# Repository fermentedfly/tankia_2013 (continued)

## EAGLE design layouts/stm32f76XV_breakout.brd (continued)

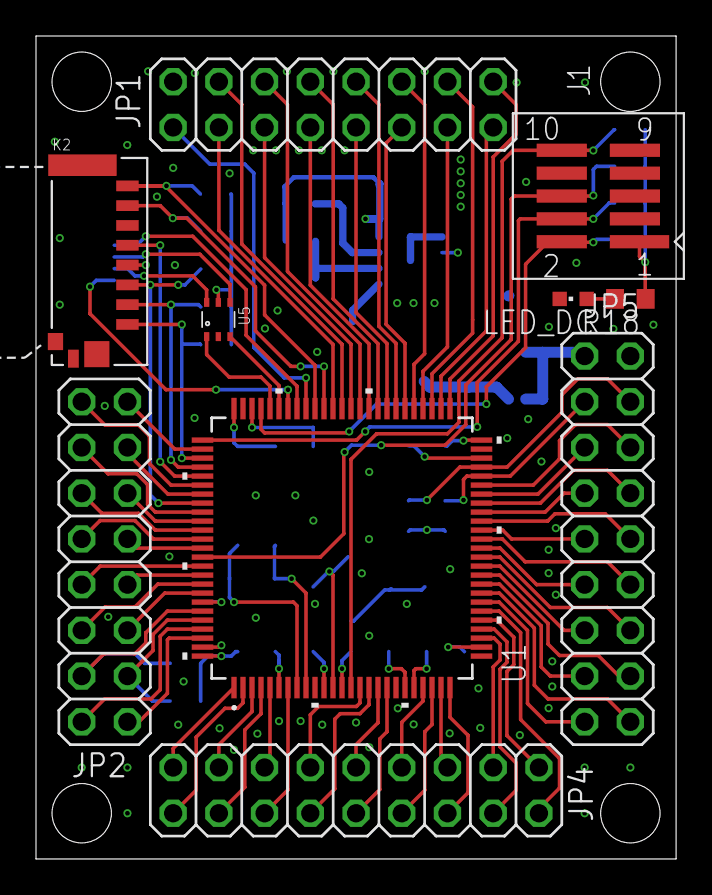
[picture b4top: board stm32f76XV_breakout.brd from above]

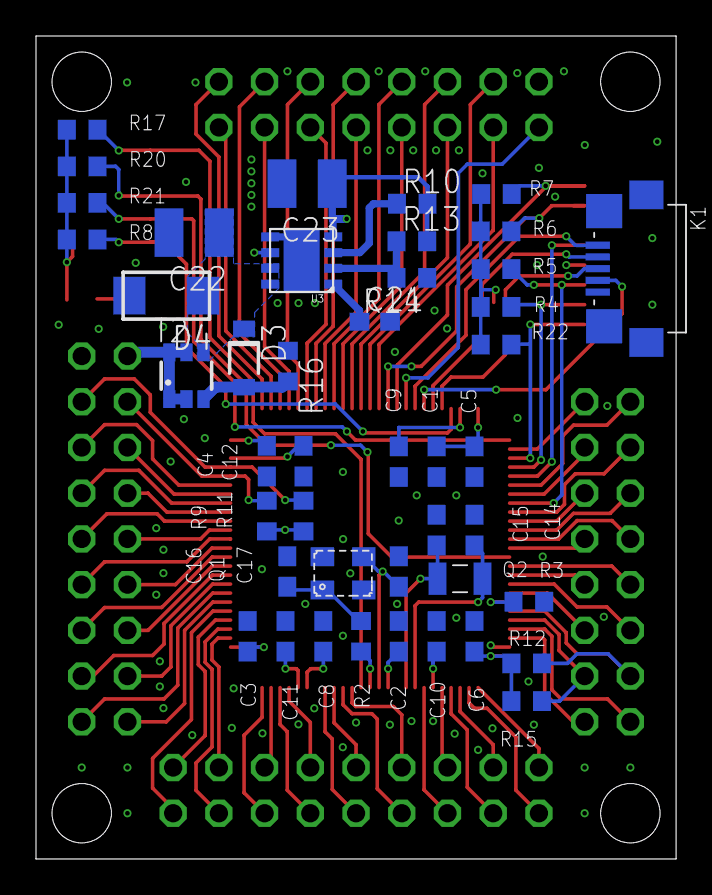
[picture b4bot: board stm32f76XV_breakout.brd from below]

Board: 4 copper layers, 35.6 x 45.7 mm, 54 parts (44 on the bottom side), 98 nets.

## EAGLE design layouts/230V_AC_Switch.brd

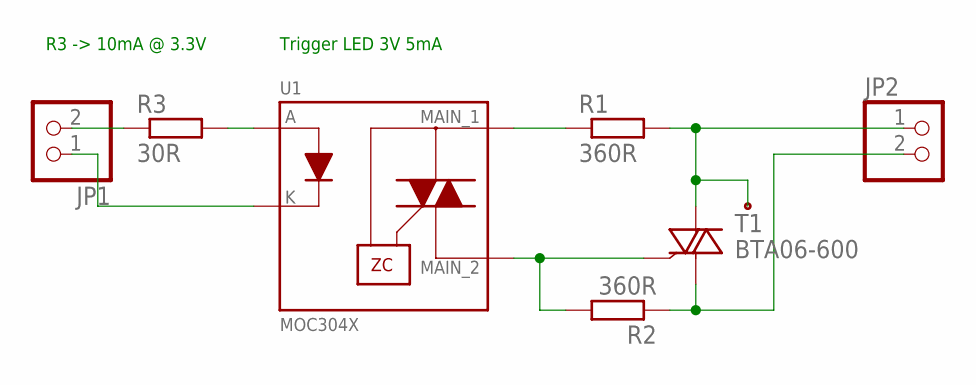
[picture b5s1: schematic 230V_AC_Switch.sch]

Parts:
JP1, JP2: PINHD-1X2; 1X02
R1, R2: 360R; R1206
R3: 30R; R0603
T1: BTA06-600; TO220AB
U1: MOC304X; PDIP

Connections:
EN_+: JP1.2, R3.1
EN_-: JP1.1, U1.2 (K)
unnamed: R2.2, T1.3 (G), U1.4 (MAIN_2)
unnamed: R1.1, U1.6 (MAIN_1)
unnamed: R3.2, U1.1 (A)
OUT: JP2.2, R2.1, T1.1 (A1)
VAC: JP2.1, R1.2, T1.2 (A2), T1.PAD

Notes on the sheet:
Trigger LED 3V 5mA
R3 -> 10mA @ 3.3V

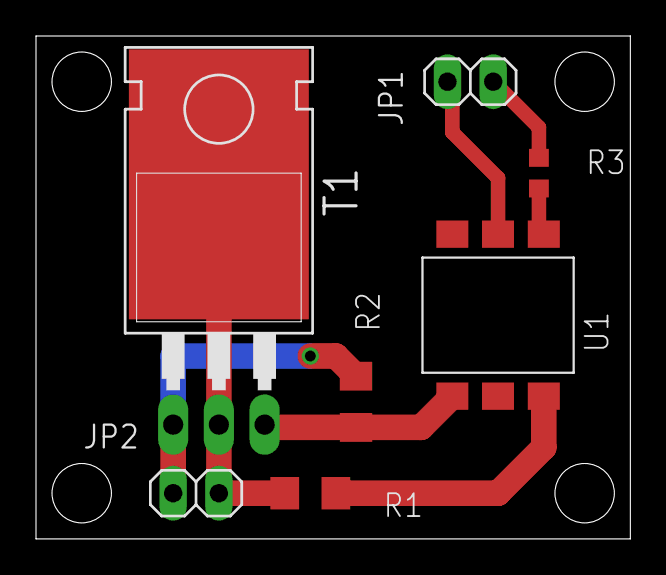
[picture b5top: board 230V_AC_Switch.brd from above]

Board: 2 copper layers, 33.0 x 27.9 mm, 7 parts (0 on the bottom side), 7 nets.

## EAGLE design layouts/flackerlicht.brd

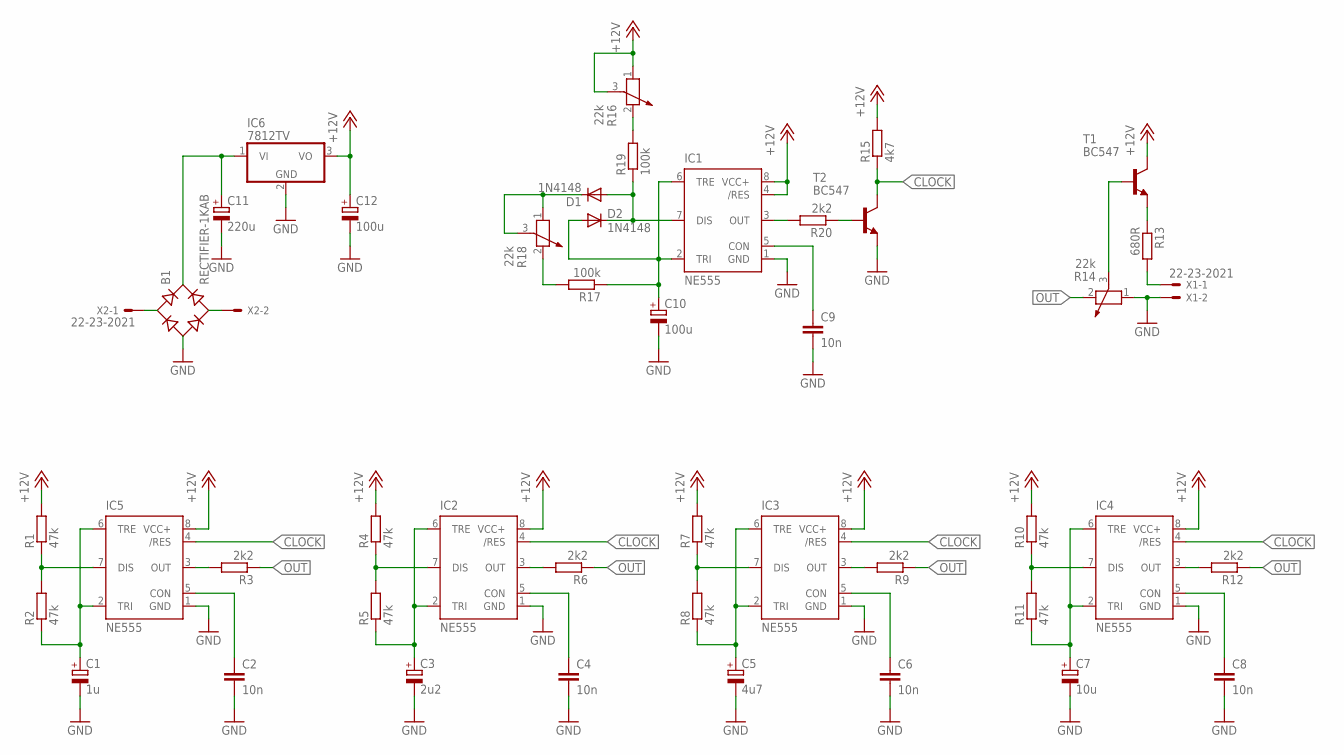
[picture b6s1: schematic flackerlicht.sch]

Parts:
B1: RECTIFIER-1KAB; 1KAB
C1: 1u; E2,5-6
C2, C4, C6, C8, C9: 10n; C050-035X075
C3: 2u2; E2,5-6
C5: 4u7; E2,5-6
C7: 10u; E2,5-6
C10, C12: 100u; E3,5-8
C11: 220u; E3,5-8
D1, D2: 1N4148; DO35-10
IC1, IC2, IC3, IC4, IC5: NE555; DIL-08
IC6: 7812TV; TO220V
R1, R2, R4, R5, R7, R8, R10, R11: 47k; 0309/10
R3, R6, R9, R12, R20: 2k2; 0309/10
R13: 680R; 0309/10
R14, R16, R18: 22k; PT-10
R15: 4k7; 0309/10
R17, R19: 100k; 0309/10
T1, T2: BC547; TO92
X1: 22-23-2021
X2: 22-23-2021; MPN 22-23-2021

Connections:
+12V: C12.+, IC1.4 (/RES), IC1.8 (VCC+), IC2.8 (VCC+), IC3.8 (VCC+), IC4.8 (VCC+), IC5.8 (VCC+), IC6.3 (VO), R1.2, R4.2, R7.2, R10.2, R15.2, R16.1, R16.3, T1.3 (C)
CLOCK: IC2.4 (/RES), IC3.4 (/RES), IC4.4 (/RES), IC5.4 (/RES), R15.1, T2.3 (C)
GND: B1.-, C1.-, C2.2, C3.-, C4.2, C5.-, C6.2, C7.-, C8.2, C9.2, C10.-, C11.-, C12.-, IC1.1 (GND), IC2.1 (GND), IC3.1 (GND), IC4.1 (GND), IC5.1 (GND), IC6.2 (GND), R14.1, T2.1 (E), X1.2
unnamed: IC5.7 (DIS), R1.1, R2.2
unnamed: C1.+, IC5.2 (TRI), IC5.6 (TRE), R2.1
unnamed: IC5.3 (OUT), R3.2
unnamed: C2.1, IC5.5 (CON)
unnamed: IC2.7 (DIS), R4.1, R5.2
unnamed: C3.+, IC2.2 (TRI), IC2.6 (TRE), R5.1
unnamed: IC2.3 (OUT), R6.2
unnamed: C4.1, IC2.5 (CON)
unnamed: IC3.7 (DIS), R7.1, R8.2
unnamed: C5.+, IC3.2 (TRI), IC3.6 (TRE), R8.1
unnamed: IC3.3 (OUT), R9.2
unnamed: C6.1, IC3.5 (CON)
unnamed: IC4.7 (DIS), R10.1, R11.2
unnamed: C7.+, IC4.2 (TRI), IC4.6 (TRE), R11.1
unnamed: IC4.3 (OUT), R12.2
unnamed: C8.1, IC4.5 (CON)
unnamed: R13.1, T1.1 (E)
unnamed: R13.2, X1.1
unnamed: R14.3, T1.2 (B)
unnamed: IC1.3 (OUT), R20.2
unnamed: C9.1, IC1.5 (CON)
unnamed: D1.A, D2.C, IC1.7 (DIS), R19.1
unnamed: C10.+, D2.A, IC1.2 (TRI), IC1.6 (TRE), R17.1
unnamed: D1.C, R18.1, R18.3
unnamed: B1.AC1, X2.1
unnamed: R17.2, R18.2
unnamed: R16.2, R19.2
unnamed: B1.AC2, X2.2
unnamed: B1.+, C11.+, IC6.1 (VI)
unnamed: R20.1, T2.2 (B)
OUT: R3.1, R6.1, R9.1, R12.1, R14.2

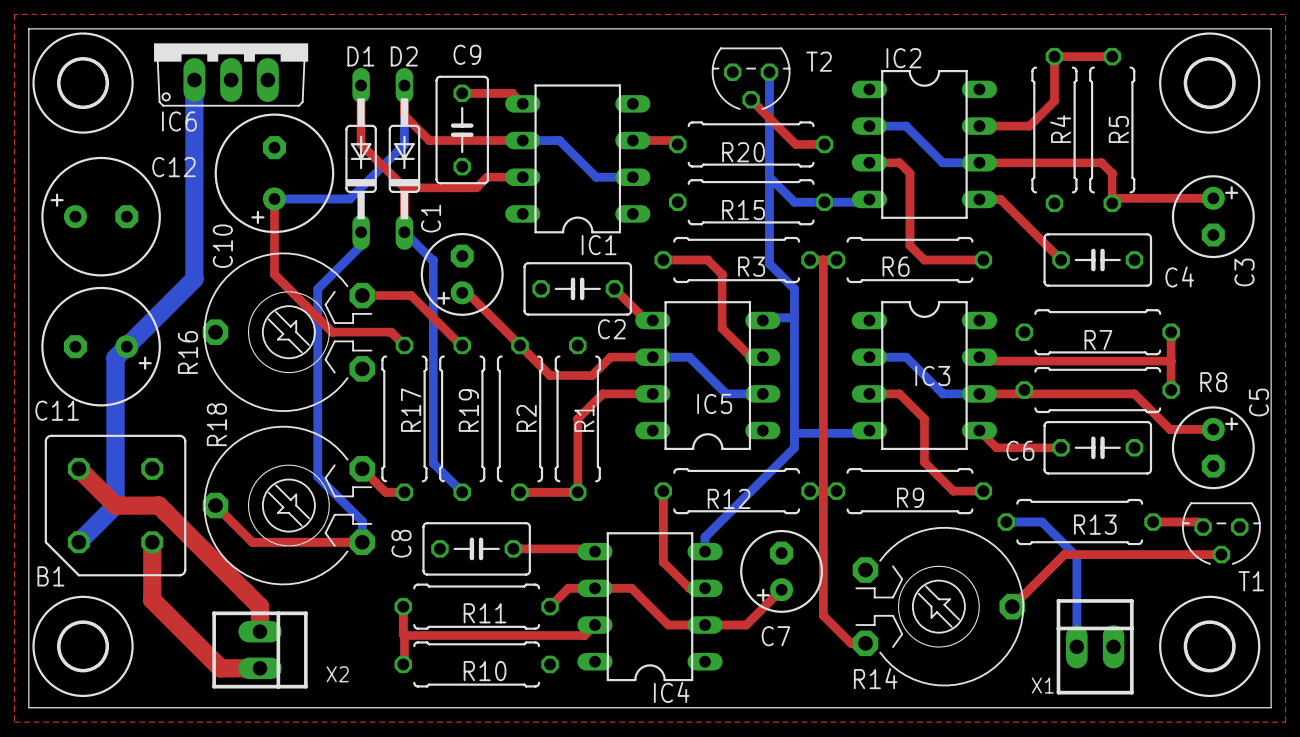
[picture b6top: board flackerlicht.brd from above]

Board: 2 copper layers, 86.0 x 47.0 mm, 49 parts (0 on the bottom side), 34 nets.

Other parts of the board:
U$1, U$2, U$3, U$4: 3,2

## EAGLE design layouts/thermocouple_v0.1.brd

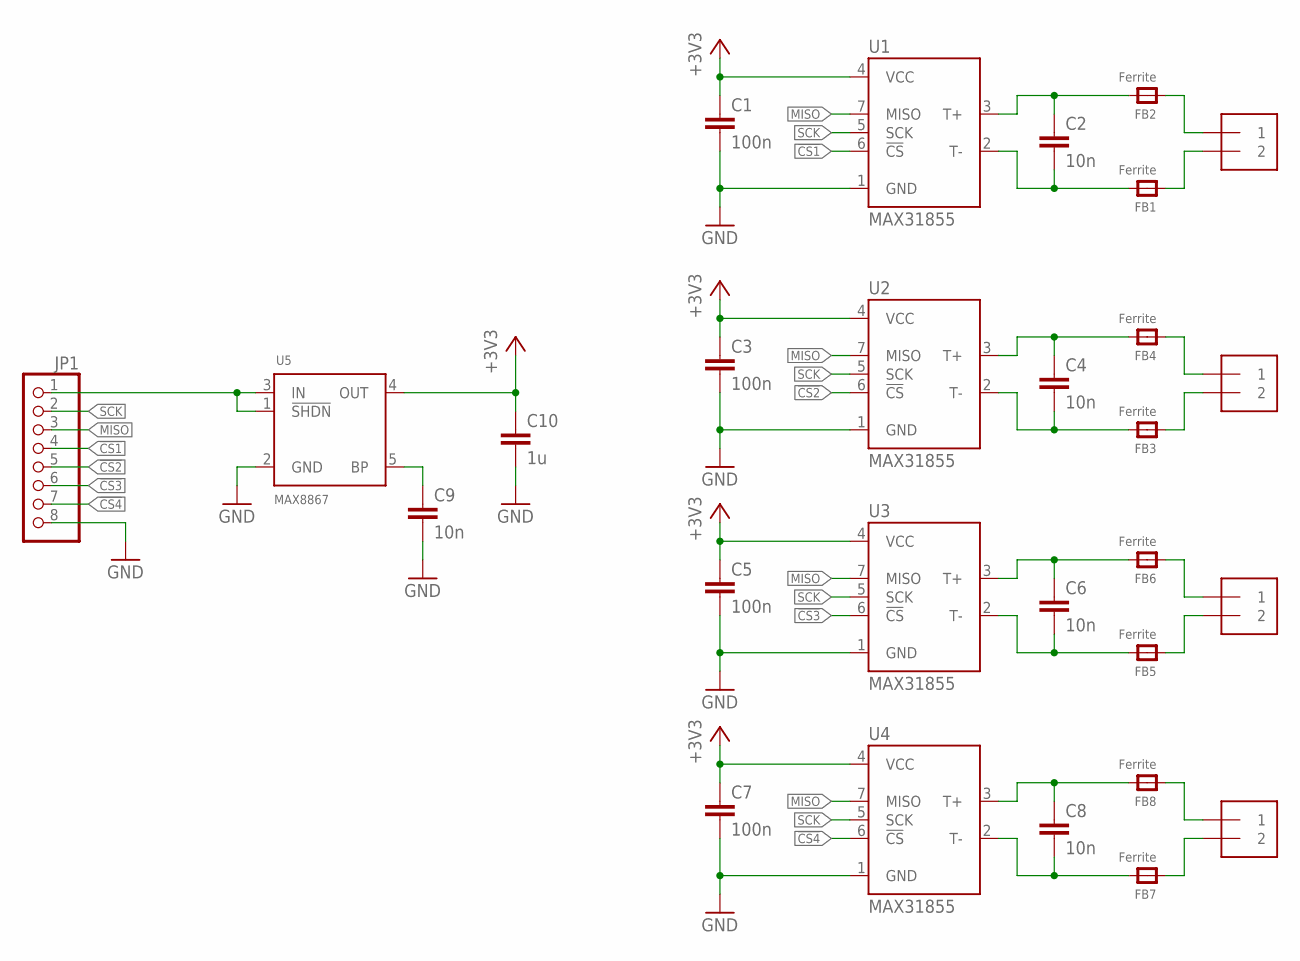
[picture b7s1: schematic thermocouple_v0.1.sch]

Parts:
C1, C3, C5, C7: 100n; C0603
C2, C4, C6, C8, C9: 10n; C0603
C10: 1u; C0603
FB1, FB2, FB3, FB4, FB5, FB6, FB7, FB8: Ferrite; _0805
J1, J2, J3, J4: 1X2-3.5MM
JP1: PINHD-1X8; 1X08
U1, U2, U3, U4: MAX31855; SO08
U5: MAX8867; SOT23-5L

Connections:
!CS1: JP1.4, U1.6 (!CS)
!CS2: JP1.5, U2.6 (!CS)
!CS3: JP1.6, U3.6 (!CS)
!CS4: JP1.7, U4.6 (!CS)
+3V3: C1.1, C3.1, C5.1, C7.1, C10.1, U1.4 (VCC), U2.4 (VCC), U3.4 (VCC), U4.4 (VCC), U5.4 (OUT)
GND: C1.2, C3.2, C5.2, C7.2, C9.2, C10.2, JP1.8, U1.1 (GND), U2.1 (GND), U3.1 (GND), U4.1 (GND), U5.2 (GND)
MISO: JP1.3, U1.7 (MISO), U2.7 (MISO), U3.7 (MISO), U4.7 (MISO)
unnamed: FB1.1, J1.2
unnamed: C2.2, FB1.2, U1.2 (T-)
unnamed: FB3.1, J2.2
unnamed: FB2.1, J1.1
unnamed: C2.1, FB2.2, U1.3 (T+)
unnamed: FB4.1, J2.1
unnamed: C4.1, FB4.2, U2.3 (T+)
unnamed: C4.2, FB3.2, U2.2 (T-)
unnamed: FB5.1, J3.2
unnamed: FB6.1, J3.1
unnamed: C6.1, FB6.2, U3.3 (T+)
unnamed: C6.2, FB5.2, U3.2 (T-)
unnamed: FB7.1, J4.2
unnamed: FB8.1, J4.1
unnamed: C8.1, FB8.2, U4.3 (T+)
unnamed: C8.2, FB7.2, U4.2 (T-)
unnamed: C9.1, U5.5 (BP)
unnamed: JP1.1, U5.1 (!SHDN), U5.3 (IN)
SCK: JP1.2, U1.5 (SCK), U2.5 (SCK), U3.5 (SCK), U4.5 (SCK)

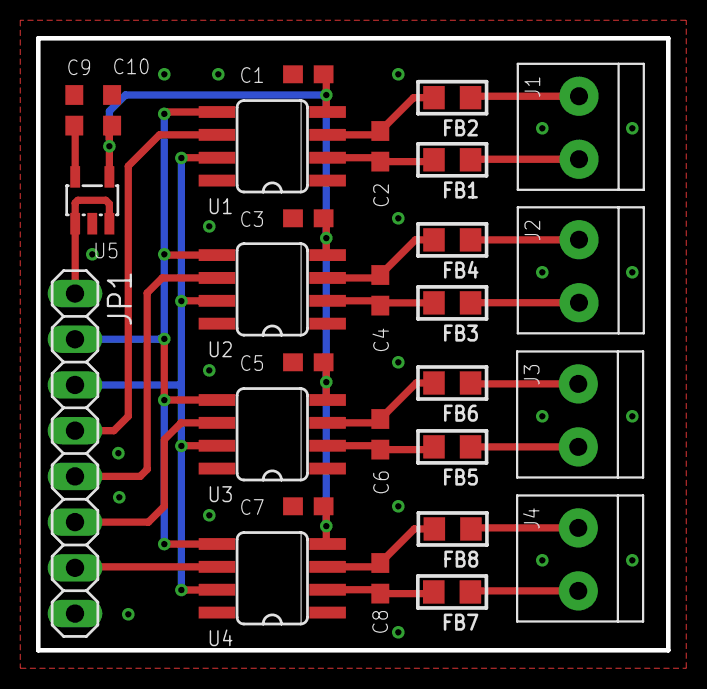
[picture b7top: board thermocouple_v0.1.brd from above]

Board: 2 copper layers, 35.0 x 34.0 mm, 28 parts (0 on the bottom side), 26 nets.

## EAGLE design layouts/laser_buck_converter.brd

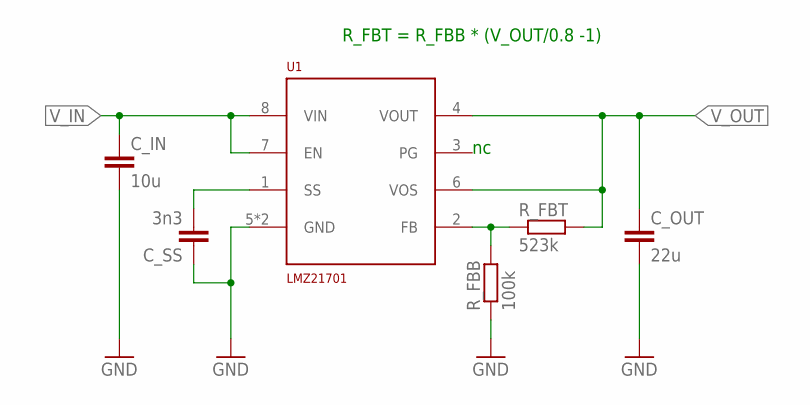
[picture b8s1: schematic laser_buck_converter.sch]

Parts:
C_IN: 10u; C0603
C_OUT: 22u; C0603
C_SS: 3n3; C0402
R_FBB: 100k; R0402
R_FBT: 523k; R0402
U1: LMZ21701; SIL0008E

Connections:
GND: C_IN.2, C_OUT.2, C_SS.1, R_FBB.1, U1.5 (GND), U1.PAD (GND)
unnamed: C_SS.2, U1.1 (SS)
unnamed: R_FBB.2, R_FBT.1, U1.2 (FB)
V_IN: C_IN.1, U1.7 (EN), U1.8 (VIN)
V_OUT: C_OUT.1, R_FBT.2, U1.4 (VOUT), U1.6 (VOS)

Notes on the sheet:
R_FBT = R_FBB * (V_OUT/0.8 -1)

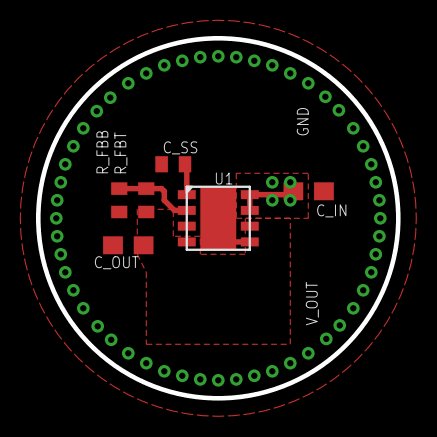
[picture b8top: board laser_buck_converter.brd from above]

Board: 2 copper layers, 20.0 x 20.0 mm, 6 parts (0 on the bottom side), 5 nets.

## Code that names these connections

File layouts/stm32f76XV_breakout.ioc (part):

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Mcu.Name=STM32F767V(G-I)Tx
Mcu.Package=LQFP100
Mcu.UserName=STM32F767VITx
PA0/WKUP.Mode=CTS_RTS
PA0/WKUP.Signal=USART2_CTS
PA1.Mode=CTS_RTS
PA1.Signal=USART2_RTS
PA10.Mode=OTG/Dual_Role_Device
PA10.Signal=USB_OTG_FS_ID
PA11.Mode=OTG/Dual_Role_Device
PA11.Signal=USB_OTG_FS_DM
PA12.Mode=OTG/Dual_Role_Device
PA12.Signal=USB_OTG_FS_DP
PA13.Mode=Trace_Asynchronous_SW
PA13.Signal=SYS_JTMS-SWDIO
PA14.Mode=Trace_Asynchronous_SW
PA14.Signal=SYS_JTCK-SWCLK
PA2.Mode=Asynchronous
PA2.Signal=USART2_TX
PA3.Mode=Asynchronous
PA3.Signal=USART2_RX
PA4.Mode=NSS_Signal_Hard_Output
PA4.Signal=SPI1_NSS
PA5.Mode=Full_Duplex_Master
PA5.Signal=SPI1_SCK
PA6.Mode=Full_Duplex_Master
PA6.Signal=SPI1_MISO
PA7.Mode=Full_Duplex_Master
PA7.Signal=SPI1_MOSI
PA8.Mode=Synchronous
PA8.Signal=USART1_CK
PA9.Mode=Activate_VBUS
PA9.Signal=USB_OTG_FS_VBUS
PB10.Mode=I2C
PB10.Signal=I2C2_SCL
PB11.Mode=I2C
PB11.Signal=I2C2_SDA
PB12.Mode=NSS_Signal_Hard_Output
PB12.Signal=SPI2_NSS
PB13.Mode=Full_Duplex_Master
PB13.Signal=SPI2_SCK
PB14.Mode=Full_Duplex_Master
PB14.Signal=SPI2_MISO
PB15.Mode=Full_Duplex_Master
PB15.Signal=SPI2_MOSI
PB3.Mode=Trace_Asynchronous_SW
PB3.Signal=SYS_JTDO-SWO
PB6.Mode=Synchronous
PB6.Signal=USART1_TX
PB7.Mode=Synchronous
PB7.Signal=USART1_RX
PB8.Mode=I2C
PB8.Signal=I2C1_SCL
PB9.Mode=I2C
PB9.Signal=I2C1_SDA
PC10.Mode=SD_4_bits_Wide_bus
PC10.Signal=SDMMC1_D2
PC11.Mode=SD_4_bits_Wide_bus
PC11.Signal=SDMMC1_D3
PC12.Mode=SD_4_bits_Wide_bus
PC12.Signal=SDMMC1_CK
PC14/OSC32_IN.Mode=LSE-External-Oscillator
PC14/OSC32_IN.Signal=RCC_OSC32_IN
PC15/OSC32_OUT.Mode=LSE-External-Oscillator
PC15/OSC32_OUT.Signal=RCC_OSC32_OUT
PC6.Mode=Asynchronous
PC6.Signal=USART6_TX
PC7.Mode=Asynchronous
PC7.Signal=USART6_RX
PC8.Mode=SD_4_bits_Wide_bus
PC8.Signal=SDMMC1_D0
PC9.Mode=SD_4_bits_Wide_bus
PC9.Signal=SDMMC1_D1
PD0.Mode=Master
PD0.Signal=CAN1_RX
PD1.Mode=Master
PD1.Signal=CAN1_TX
PD10.Signal=USART3_CK
PD11.Mode=CTS_RTS
PD11.Signal=USART3_CTS
PD12.Mode=CTS_RTS
PD12.Signal=USART3_RTS
PD2.Mode=SD_4_bits_Wide_bus
PD2.Signal=SDMMC1_CMD
PD8.Mode=Asynchronous
PD8.Signal=USART3_TX
PD9.Mode=Asynchronous
PD9.Signal=USART3_RX
PE0.Mode=Asynchronous
PE0.Signal=UART8_RX
PE1.Mode=Asynchronous
PE1.Signal=UART8_TX
PE2.Mode=Full_Duplex_Master
PE2.Signal=SPI4_SCK
PE4.Mode=NSS_Signal_Hard_Output
PE4.Signal=SPI4_NSS
PE5.Mode=Full_Duplex_Master
PE5.Signal=SPI4_MISO
PE6.Mode=Full_Duplex_Master
PE6.Signal=SPI4_MOSI
PE7.Mode=Asynchronous
PE7.Signal=UART7_RX
PE8.Mode=Asynchronous
PE8.Signal=UART7_TX
PH0/OSC_IN.Mode=HSE-External-Oscillator
PH0/OSC_IN.Signal=RCC_OSC_IN
PH1/OSC_OUT.Mode=HSE-External-Oscillator
PH1/OSC_OUT.Signal=RCC_OSC_OUT
RCC.HSE_VALUE=25000000
RCC.SYSCLKFreq_VALUE=216000000
RCC.SYSCLKSource=RCC_SYSCLKSOURCE_PLLCLK

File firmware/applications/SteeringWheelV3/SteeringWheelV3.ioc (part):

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Mcu.Name=STM32F405RGTx
Mcu.Package=LQFP64
Mcu.UserName=STM32F405RGTx
PA10.Mode=OTG/Dual_Role_Device
PA10.Signal=USB_OTG_FS_ID
PA11.Mode=OTG/Dual_Role_Device
PA11.Signal=USB_OTG_FS_DM
PA12.Mode=OTG/Dual_Role_Device
PA12.Signal=USB_OTG_FS_DP
PA13.Mode=Trace_Asynchronous_SW
PA13.Signal=SYS_JTMS-SWDIO
PA14.Mode=Trace_Asynchronous_SW
PA14.Signal=SYS_JTCK-SWCLK
PA15.GPIOParameters=GPIO_Label
PA15.GPIO_Label=eDIP_Reset
PA15.Signal=GPIO_Output
PA4.GPIOParameters=GPIO_Label
PA4.GPIO_Label=ADC1_Clutch
PA4.Signal=ADCx_IN4
PA9.Mode=Activate_VBUS
PA9.Signal=USB_OTG_FS_VBUS
PB0.GPIOParameters=GPIO_Label
PB0.GPIO_Label=MAX_Shift_Up
PB0.Signal=GPXTI0
PB1.GPIOParameters=GPIO_Label
PB1.GPIO_Label=MAX_Plus
PB1.Signal=GPXTI1
PB10.GPIOParameters=GPIO_Label,GPIO_ModeDefaultEXTI
PB10.GPIO_Label=nMAX_CH
PB10.GPIO_ModeDefaultEXTI=GPIO_MODE_IT_FALLING
PB10.Signal=GPXTI10
PB12.GPIOParameters=GPIO_PuPd,GPIO_Label
PB12.GPIO_Label=LED_0
PB12.GPIO_PuPd=GPIO_PULLUP
PB12.Signal=GPIO_Output
PB13.GPIOParameters=GPIO_PuPd,GPIO_Label
PB13.GPIO_Label=LED_1
PB13.GPIO_PuPd=GPIO_PULLUP
PB13.Signal=GPIO_Output
PB14.GPIOParameters=GPIO_PuPd,GPIO_Label
PB14.GPIO_Label=LED_2
PB14.GPIO_PuPd=GPIO_PULLUP
PB14.Signal=GPIO_Output
PB15.GPIOParameters=GPIO_PuPd,GPIO_Label
PB15.GPIO_Label=LED_3
PB15.GPIO_PuPd=GPIO_PULLUP
PB15.Signal=GPIO_Output
PB2.GPIOParameters=GPIO_Label
PB2.GPIO_Label=MAX_Enter
PB2.Signal=GPXTI2
PB3.Mode=Trace_Asynchronous_SW
PB3.Signal=SYS_JTDO-SWO
PB6.Mode=I2C
PB6.Signal=I2C1_SCL
PB7.Mode=I2C
PB7.Signal=I2C1_SDA
PB8.Mode=Master
PB8.Signal=CAN1_RX
PB9.Mode=Master
PB9.Signal=CAN1_TX
PC0.GPIOParameters=GPIO_Label
PC0.GPIO_Label=EN_5V
PC0.Signal=GPIO_Output
PC10.Mode=Asynchronous
PC10.Signal=UART4_TX
PC11.Mode=Asynchronous
PC11.Signal=UART4_RX
PC4.GPIOParameters=GPIO_Label
PC4.GPIO_Label=MAX_SHIFT_DOWN
PC4.Signal=GPXTI4
PC5.GPIOParameters=GPIO_Label
PC5.GPIO_Label=MAX_MINUS
PC5.Signal=GPXTI5
PH0-OSC_IN.Mode=HSE-External-Oscillator
PH0-OSC_IN.Signal=RCC_OSC_IN
PH1-OSC_OUT.Mode=HSE-External-Oscillator
PH1-OSC_OUT.Signal=RCC_OSC_OUT
RCC.HSE_VALUE=25000000
RCC.SYSCLKFreq_VALUE=168000000
RCC.SYSCLKSource=RCC_SYSCLKSOURCE_PLLCLK
board=SteeringWheelV3

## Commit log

2016-08-13 added design rules
2016-08-13 added libraries
2016-08-13 boneX microscope light strip
2016-08-13 thermocouple max31855 board
2016-08-20 added buck converter for laser board (layout designed to contact to Li-Ion 18650 Cylindrical)
2016-09-01 fixed wrong name of MAX8867
2016-09-01 fixed eagle errors due to upgrade to 6.5
2016-09-13 added tankia 2013 steering wheel v3
2016-10-11 added todo for steering wheel 2013
2016-11-08 added basic project for steering wheel
2016-11-11 CAN1 ok in loopback mode
2016-11-11 changed project structure
2016-11-12 implemented more can messages
2016-11-13 removed cmsis_os
2016-11-13 fixed broken scheduler start
2016-11-22 restructured to support multiple projects, SEGGER Systemview working
2016-11-22 can driver split between application and driver
2016-11-22 added usb driver
2016-11-22 forgot to save main :-)
2016-11-23 another round of restructureing + MAX7313 driver
2016-11-23 added v3.1 layout with bugfixes (i2c pullup, led resistors)
2016-11-24 added rpm decoding
2016-11-25 added adc for clutch conversion and basic processing
2016-12-10 begin display implementation
2017-01-08 added stm32f7 breakout board
2017-01-08 added samtec jtag debug connector
2017-01-08 some work at display
2017-01-09 aligned all pinheaders to 2.54mm
2017-01-21 changed display navigation strategy
2017-02-13 added complete hal drivers, added superled driver project
2017-02-13 some further work at steering wheel
2017-02-13 added triac driver board
2017-03-25 updated layout, changed old 20 pin IDC to new 10 pin debug
2017-08-12 fixed wrong ifdefs in drv_usart, removed program mode macro
2017-08-12 can send working, problems with receive
2017-08-13 changed can library too vifdaq can lib
2017-08-20 can now functional, added update bargraph to display driver
2017-09-18 buttons + / shift up / enter ok, left side buttons not working, leds not working
2017-10-02 added speed and rpm to racepage
2017-10-05 added scaling for clutch adc
2017-10-05 added oil and water temperature to racepage
2017-10-05 fixed bad can IDs of clutch and switch, fixed clutch reversed, disabled LEDS
2017-10-14 added MS4 function sheet, fixed speed calcuation
2017-10-16 added shift through plus / minus in racepage
2017-10-16 added clutch setup menu, new scheme for value edit mode
2017-10-17 added clutch configuration can message transmit
2017-10-19 disabled can rx task, message parsing directly in ISR
2017-10-24 added breakout for TPS22810
2018-11-23 change repo to contain only tankia stuff
